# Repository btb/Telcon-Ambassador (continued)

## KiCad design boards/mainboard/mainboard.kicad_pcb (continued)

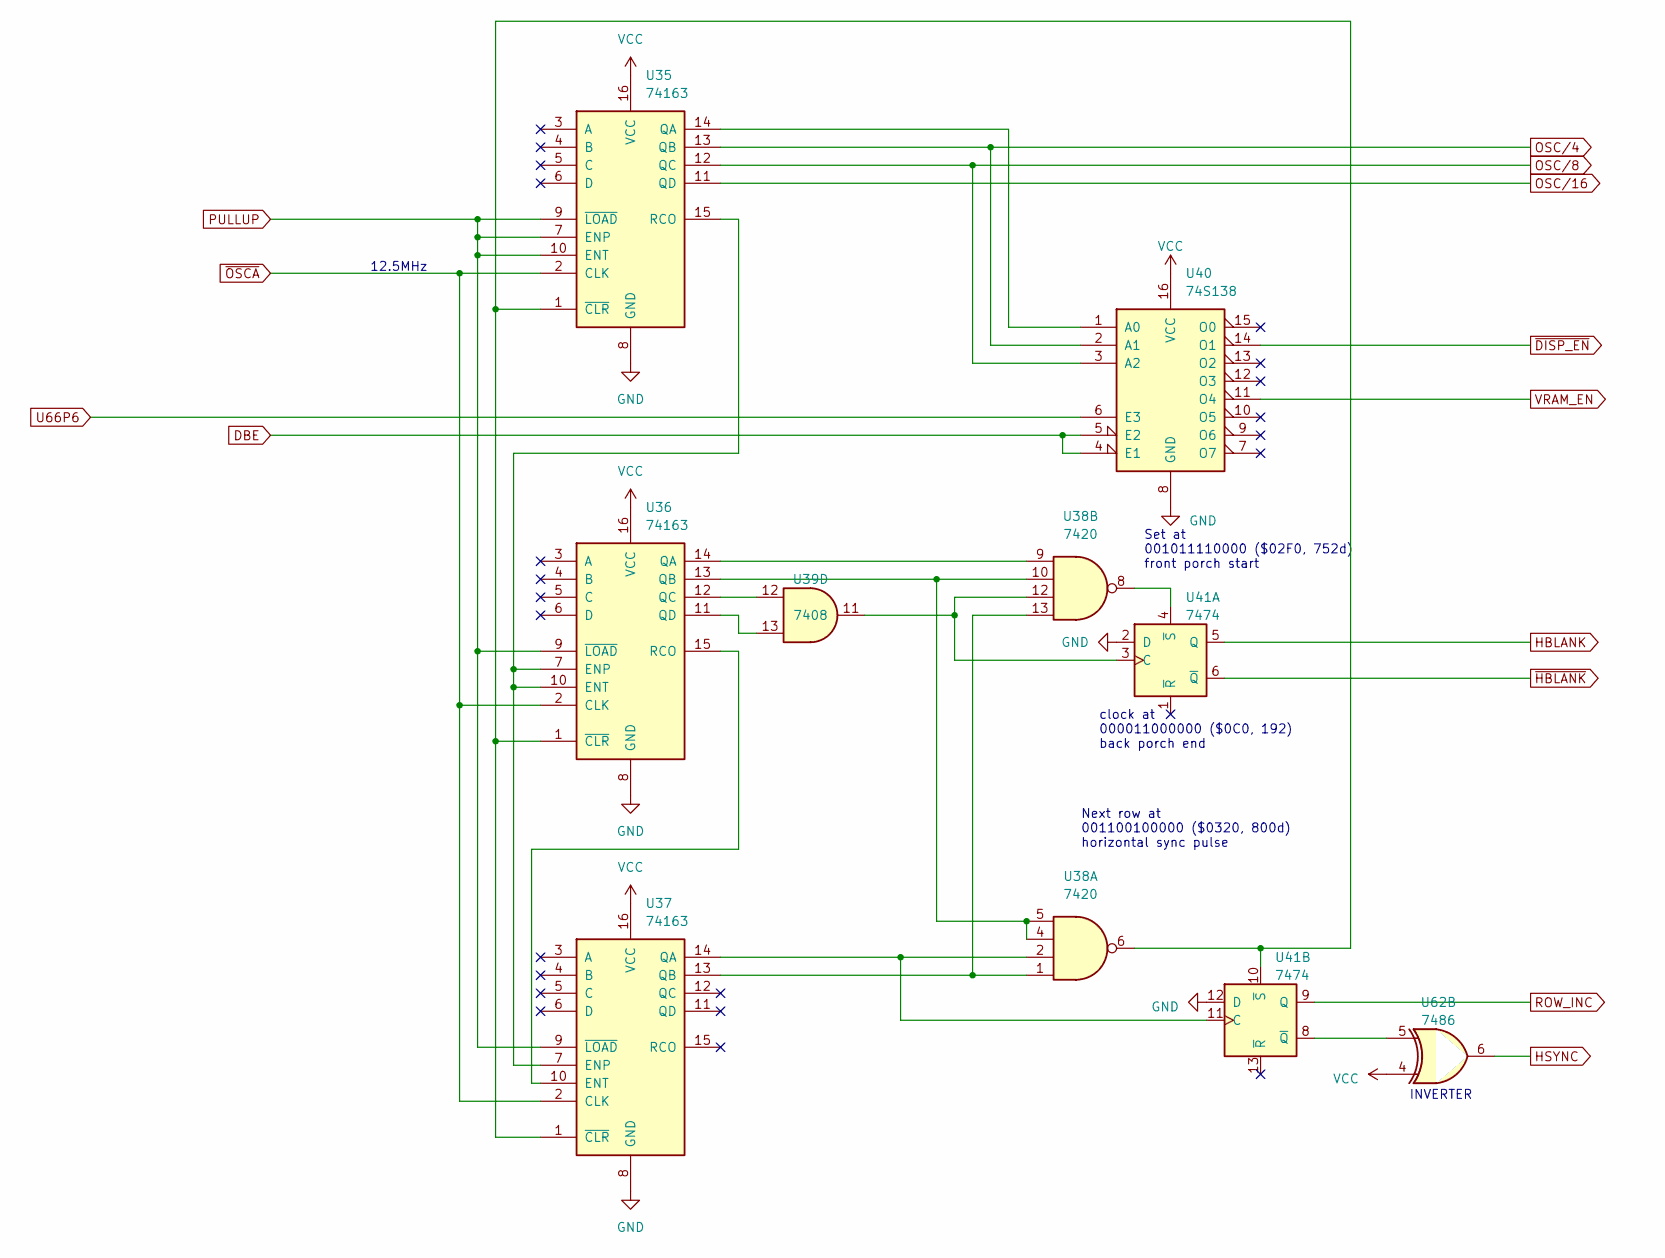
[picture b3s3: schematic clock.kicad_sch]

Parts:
U35, U36, U37: 74163; DIP-16_W7.62mm
U38: 7420; DIP-14_W7.62mm
U39: 7408; DIP-14_W7.62mm
U40: 74S138; DIP-16_W7.62mm
U41: 7474; DIP-14_W7.62mm
U62: 7486; DIP-14_W7.62mm

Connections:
DBE: U40.4 (E1), U40.5 (E2); also elsewhere on the board
GND: U35.8 (GND), U36.8 (GND), U37.8 (GND), U40.8 (GND), U41.2 (D), U41.12 (D); also elsewhere on the board
HBLANK: U41.5 (Q); also elsewhere on the board
HSYNC: U62.6; also elsewhere on the board
unnamed: U35.14 (QA), U40.1 (A0)
unnamed: U35.15 (RCO), U36.7 (ENP), U36.10 (ENT), U37.7 (ENP)
unnamed: U35.1 (~CLR), U36.1 (~CLR), U37.1 (~CLR), U38.6, U41.10 (~S)
unnamed: U36.14 (QA), U38.9
unnamed: U36.13 (QB), U38.4, U38.5, U38.10
unnamed: U36.12 (QC), U39.12
unnamed: U36.11 (QD), U39.13
unnamed: U36.15 (RCO), U37.10 (ENT)
unnamed: U37.14 (QA), U38.2, U41.11 (C)
unnamed: U37.13 (QB), U38.1, U38.13
unnamed: U38.12, U39.11, U41.3 (C)
unnamed: U38.8, U41.4 (~S)
unnamed: U41.8 (~Q), U62.5
OSC/4: U35.13 (QB), U40.2 (A1); also elsewhere on the board
OSC/8: U35.12 (QC), U40.3 (A2); also elsewhere on the board
OSC/16: U35.11 (QD); also elsewhere on the board
PULLUP: U35.7 (ENP), U35.9 (~LOAD), U35.10 (ENT), U36.9 (~LOAD), U37.9 (~LOAD); also elsewhere on the board
ROW_INC: U41.9 (Q); also elsewhere on the board
U66P6: U40.6 (E3); also elsewhere on the board
VCC: U35.16 (VCC), U36.16 (VCC), U37.16 (VCC), U40.16 (VCC), U62.4; also elsewhere on the board
VRAM_EN: U40.11 (O4); also elsewhere on the board
~DISP_EN: U40.14 (O1); also elsewhere on the board
~HBLANK: U41.6 (~Q); also elsewhere on the board
~OSCA: U35.2 (CLK), U36.2 (CLK), U37.2 (CLK); also elsewhere on the board

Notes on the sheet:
Next row at 001100100000 ($0320, 800d) horizontal sync pulse
INVERTER
12.5MHz
clock at 000011000000 ($0C0, 192) back porch end
Set at 001011110000 ($02F0, 752d) front porch start

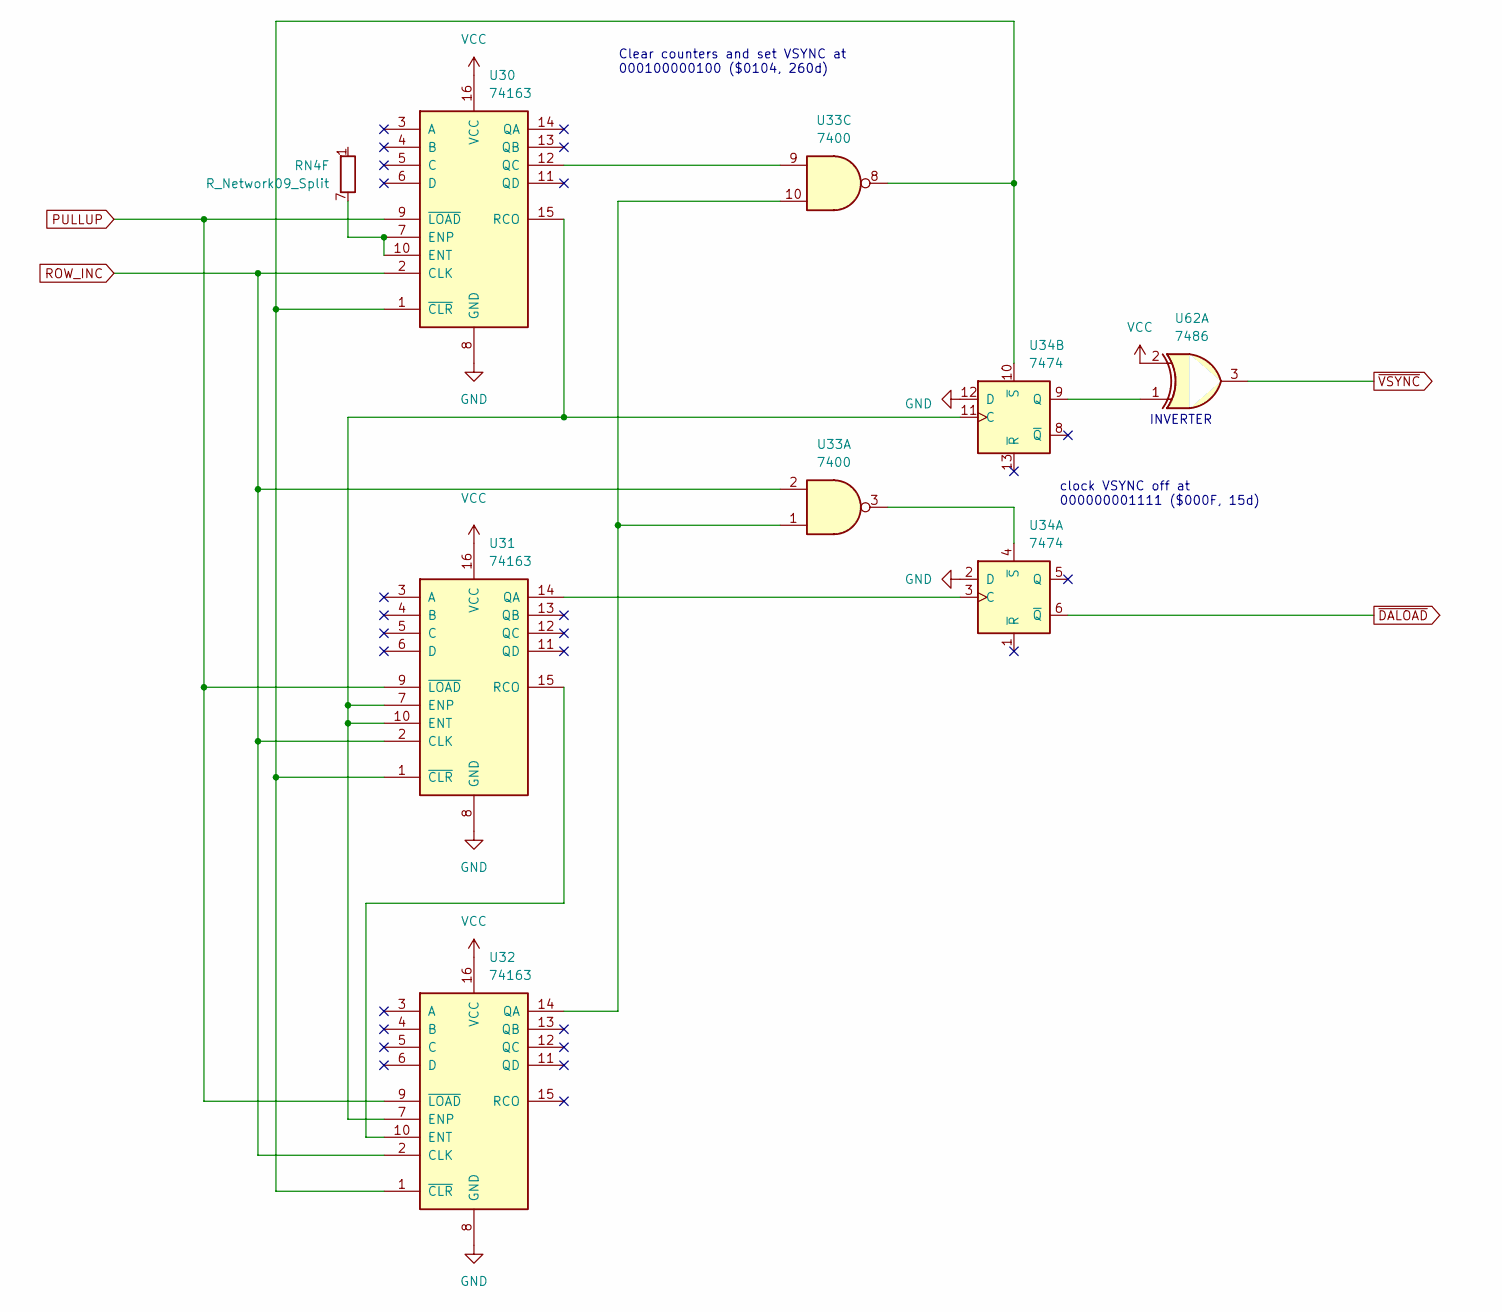
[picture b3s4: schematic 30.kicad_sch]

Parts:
RN4: R_Network09_Split; R_Array_SIP10
U30, U31, U32: 74163; DIP-16_W7.62mm
U33: 7400; DIP-14_W7.62mm
U34: 7474; DIP-14_W7.62mm
U62: 7486; DIP-14_W7.62mm

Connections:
GND: U30.8 (GND), U31.8 (GND), U32.8 (GND), U34.2 (D), U34.12 (D); also elsewhere on the board
unnamed: RN4.7 (R6.2), U30.7 (ENP), U30.10 (ENT)
unnamed: U30.12 (QC), U33.9
unnamed: U30.15 (RCO), U31.7 (ENP), U31.10 (ENT), U32.7 (ENP), U34.11 (C)
unnamed: U30.1 (~CLR), U31.1 (~CLR), U32.1 (~CLR), U33.8, U34.10 (~S)
unnamed: U31.14 (QA), U34.3 (C)
unnamed: U31.15 (RCO), U32.10 (ENT)
unnamed: U32.14 (QA), U33.1, U33.10
unnamed: U33.3, U34.4 (~S)
unnamed: U34.9 (Q), U62.1
PULLUP: U30.9 (~LOAD), U31.9 (~LOAD), U32.9 (~LOAD); also elsewhere on the board
ROW_INC: U30.2 (CLK), U31.2 (CLK), U32.2 (CLK), U33.2; also elsewhere on the board
VCC: U30.16 (VCC), U31.16 (VCC), U32.16 (VCC), U62.2; also elsewhere on the board
~DALOAD: U34.6 (~Q); also elsewhere on the board
~VSYNC: U62.3; also elsewhere on the board

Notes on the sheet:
INVERTER
Clear counters and set VSYNC at 000100000100 ($0104, 260d)
clock VSYNC off at 000000001111 ($000F, 15d)

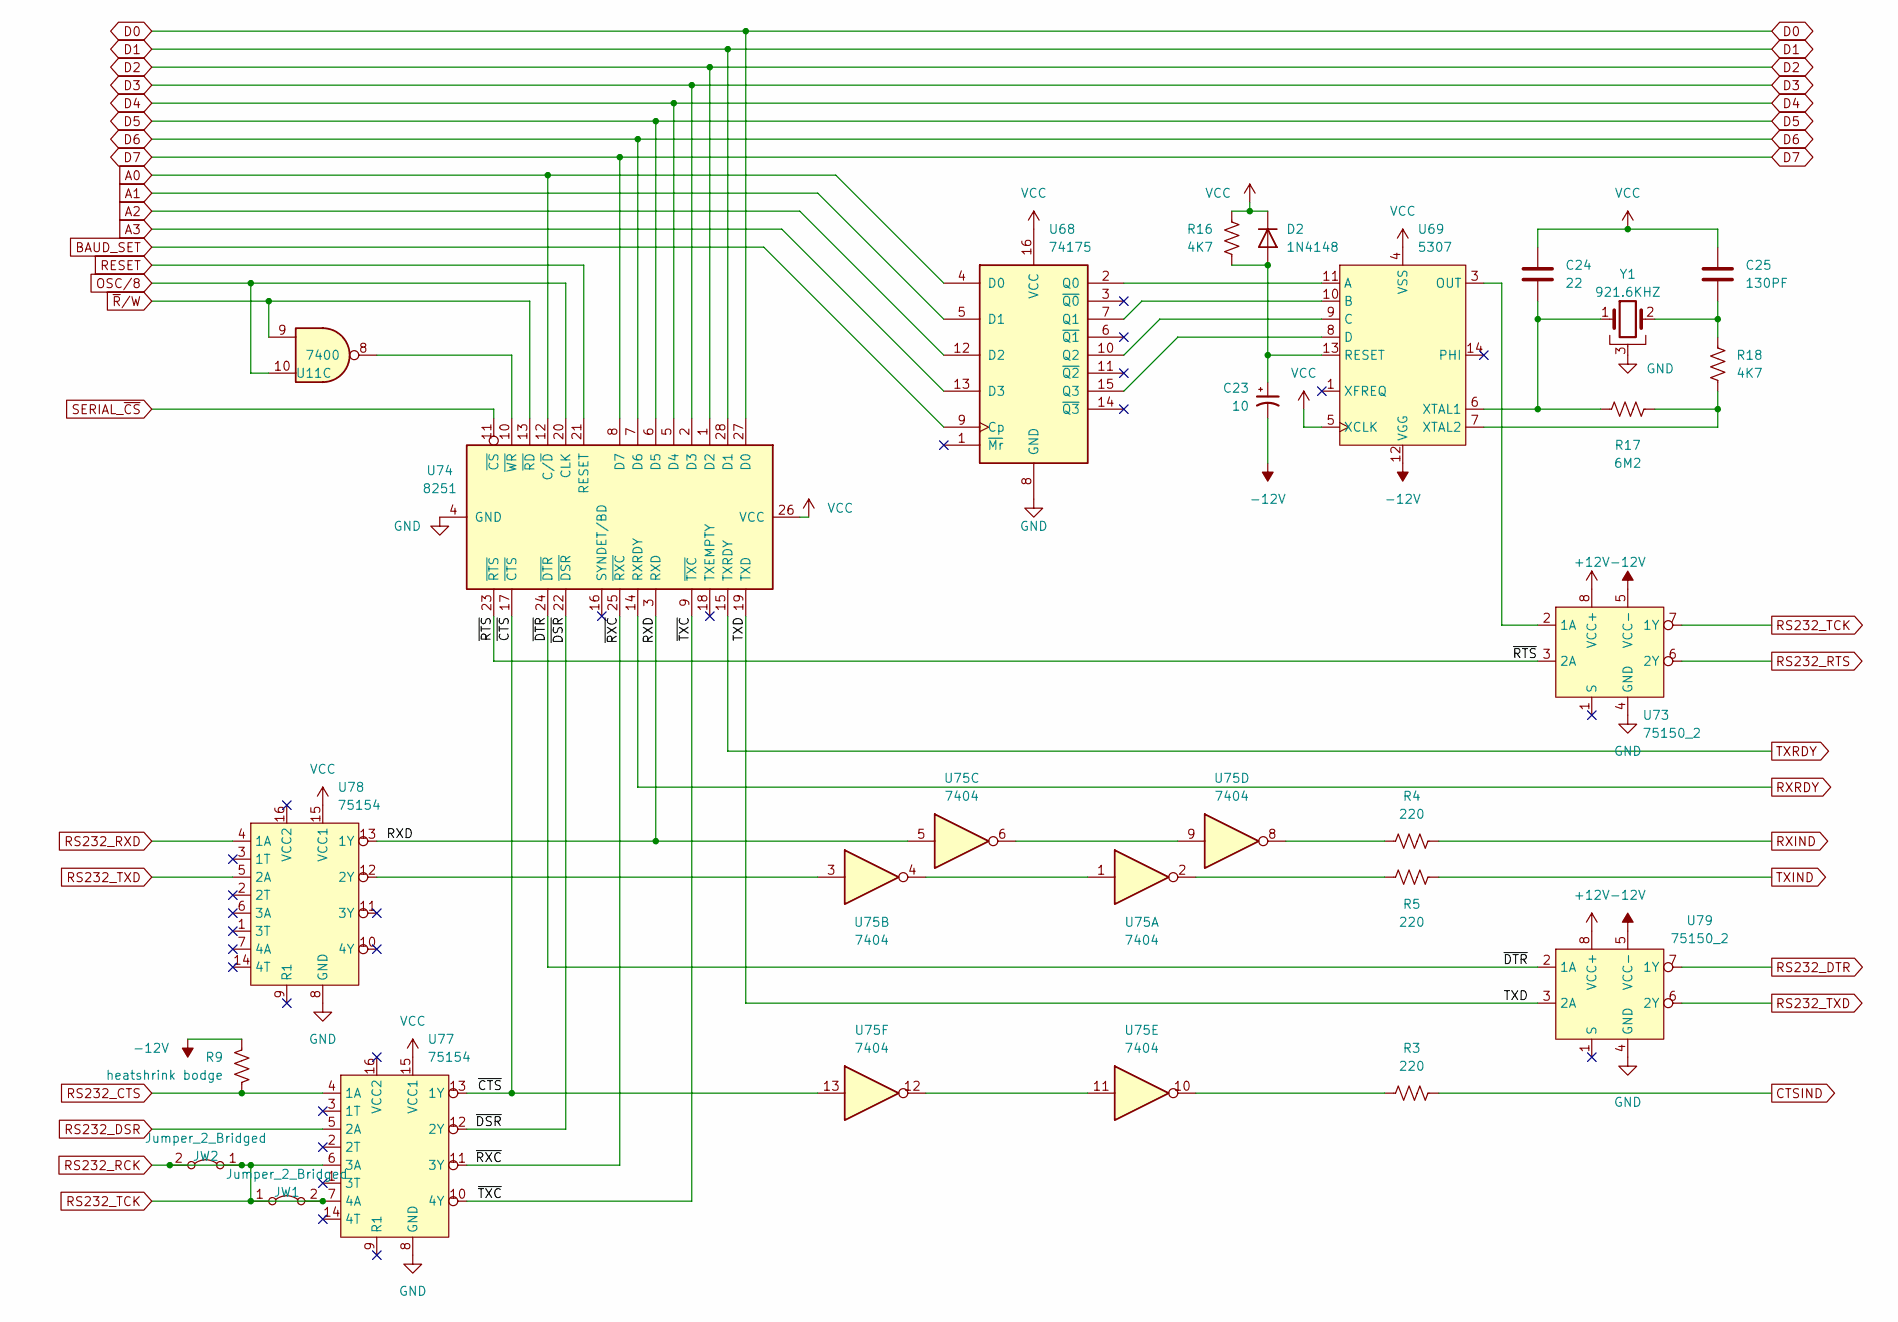
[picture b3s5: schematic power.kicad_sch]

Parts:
C23: 10; CP_Radial_Tantal_D4.5mm_P5.00mm
C24: 22; C_Disc_D11.0mm_W5.0mm_P7.50mm
C25: 130PF; C_Disc_D11.0mm_W5.0mm_P7.50mm
D2: 1N4148; D_DO-35_SOD27_P7.62mm_Horizontal
JW1: Jumper_2_Bridged; SolderWire-0.5sqmm_1x02_P10.16mm_D0.9mm_OD2.1mm
JW2: Jumper_2_Bridged; SolderWire-0.5sqmm_1x02_P12.7mm_D0.9mm_OD2.1mm
R3, R4, R5: 220; R_Axial_DIN0309_L9.0mm_D3.2mm_P12.70mm_Horizontal
R9: heatshrink bodge; R_Axial_DIN0309_L9.0mm_D3.2mm_P12.70mm_Horizontal
R16, R18: 4K7; R_Axial_DIN0309_L9.0mm_D3.2mm_P12.70mm_Horizontal
R17: 6M2; R_Axial_DIN0309_L9.0mm_D3.2mm_P12.70mm_Horizontal
U11: 7400; DIP-14_W7.62mm
U68: 74175; DIP-16_W7.62mm
U69: 5307; DIP-14_W7.62mm
U73, U79: 75150_2; DIP-8_W7.62mm
U74: 8251; DIP-28_W15.24mm
U75: 7404; DIP-14_W7.62mm
U77, U78: 75154; DIP-16_W7.62mm
Y1: 921.6KHZ; Crystal_HC33-U_Horizontal_1EP_style2

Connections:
+12V: U73.8 (VCC+), U79.8 (VCC+); also elsewhere on the board
-12V: C23.2, R9.2, U69.12 (VGG), U73.5 (VCC-), U79.5 (VCC-); also elsewhere on the board
/Serial/RXD: U74.3 (RXD), U75.5, U78.13 (1Y)
/Serial/TXD: U74.19 (TXD), U79.3 (2A)
/Serial/~CTS: U74.17 (~CTS), U75.13, U77.13 (1Y)
/Serial/~DSR: U74.22 (~DSR), U77.12 (2Y)
/Serial/~DTR: U74.24 (~DTR), U79.2 (1A)
/Serial/~RTS: U73.3 (2A), U74.23 (~RTS)
/Serial/~RXC: U74.25 (~RXC), U77.11 (3Y)
/Serial/~TXC: U74.9 (~TXC), U77.10 (4Y)
A0: U68.4 (D0), U74.12 (C/~D); also elsewhere on the board
A1: U68.5 (D1); also elsewhere on the board
A2: U68.12 (D2); also elsewhere on the board
A3: U68.13 (D3); also elsewhere on the board
BAUD_SET: U68.9 (Cp); also elsewhere on the board
CTSIND: R3.2; also elsewhere on the board
D0: U74.27 (D0); also elsewhere on the board
D1: U74.28 (D1); also elsewhere on the board
D2: U74.1 (D2); also elsewhere on the board
D3: U74.2 (D3); also elsewhere on the board
D4: U74.5 (D4); also elsewhere on the board
D5: U74.6 (D5); also elsewhere on the board
D6: U74.7 (D6); also elsewhere on the board
D7: U74.8 (D7); also elsewhere on the board
GND: U68.8 (GND), U73.4 (GND), U74.4 (GND), U77.8 (GND), U78.8 (GND), U79.4 (GND), Y1.3; also elsewhere on the board
unnamed: C25.1, R18.1, Y1.2
unnamed: C23.1, D2.2 (A), R16.1, U69.13 (RESET)
unnamed: R3.1, U75.10
unnamed: R4.1, U75.8
unnamed: R5.1, U75.2
unnamed: U68.2 (Q0), U69.11 (A)
unnamed: U68.7 (Q1), U69.10 (B)
unnamed: U68.10 (Q2), U69.9 (C)
unnamed: U68.15 (Q3), U69.8 (D)
unnamed: U69.3 (OUT), U73.2 (1A)
unnamed: C24.1, R17.1, U69.6 (XTAL1), Y1.1
unnamed: R17.2, R18.2, U69.7 (XTAL2)
unnamed: U11.8, U74.10 (~WR)
unnamed: U75.1, U75.4
unnamed: U75.6, U75.9
unnamed: U75.11, U75.12
unnamed: U75.3, U78.12 (2Y)
OSC/8: U11.10, U74.20 (CLK); also elsewhere on the board
RESET: U74.21 (RESET); also elsewhere on the board
RS232_CTS: R9.1, U77.4 (1A); also elsewhere on the board
RS232_DSR: U77.5 (2A); also elsewhere on the board
RS232_DTR: U79.7 (1Y); also elsewhere on the board
RS232_RCK: JW1.1 (A), JW1.2 (B), JW2.1 (A), JW2.2 (B), U73.7 (1Y), U77.6 (3A), U77.7 (4A); also elsewhere on the board
RS232_RTS: U73.6 (2Y); also elsewhere on the board
RS232_RXD: U78.4 (1A); also elsewhere on the board
RS232_TXD: U78.5 (2A), U79.6 (2Y); also elsewhere on the board
RXIND: R4.2; also elsewhere on the board
RXRDY: U74.14 (RXRDY); also elsewhere on the board
SERIAL_~CS: U74.11 (~CS); also elsewhere on the board
TXIND: R5.2; also elsewhere on the board
TXRDY: U74.15 (TXRDY); also elsewhere on the board
VCC: C24.2, C25.2, D2.1 (K), R16.2, U68.16 (VCC), U69.4 (VSS), U69.5 (XCLK), U74.26 (VCC), U77.15 (VCC1), U78.15 (VCC1); also elsewhere on the board
~R/W: U11.9, U74.13 (~RD); also elsewhere on the board

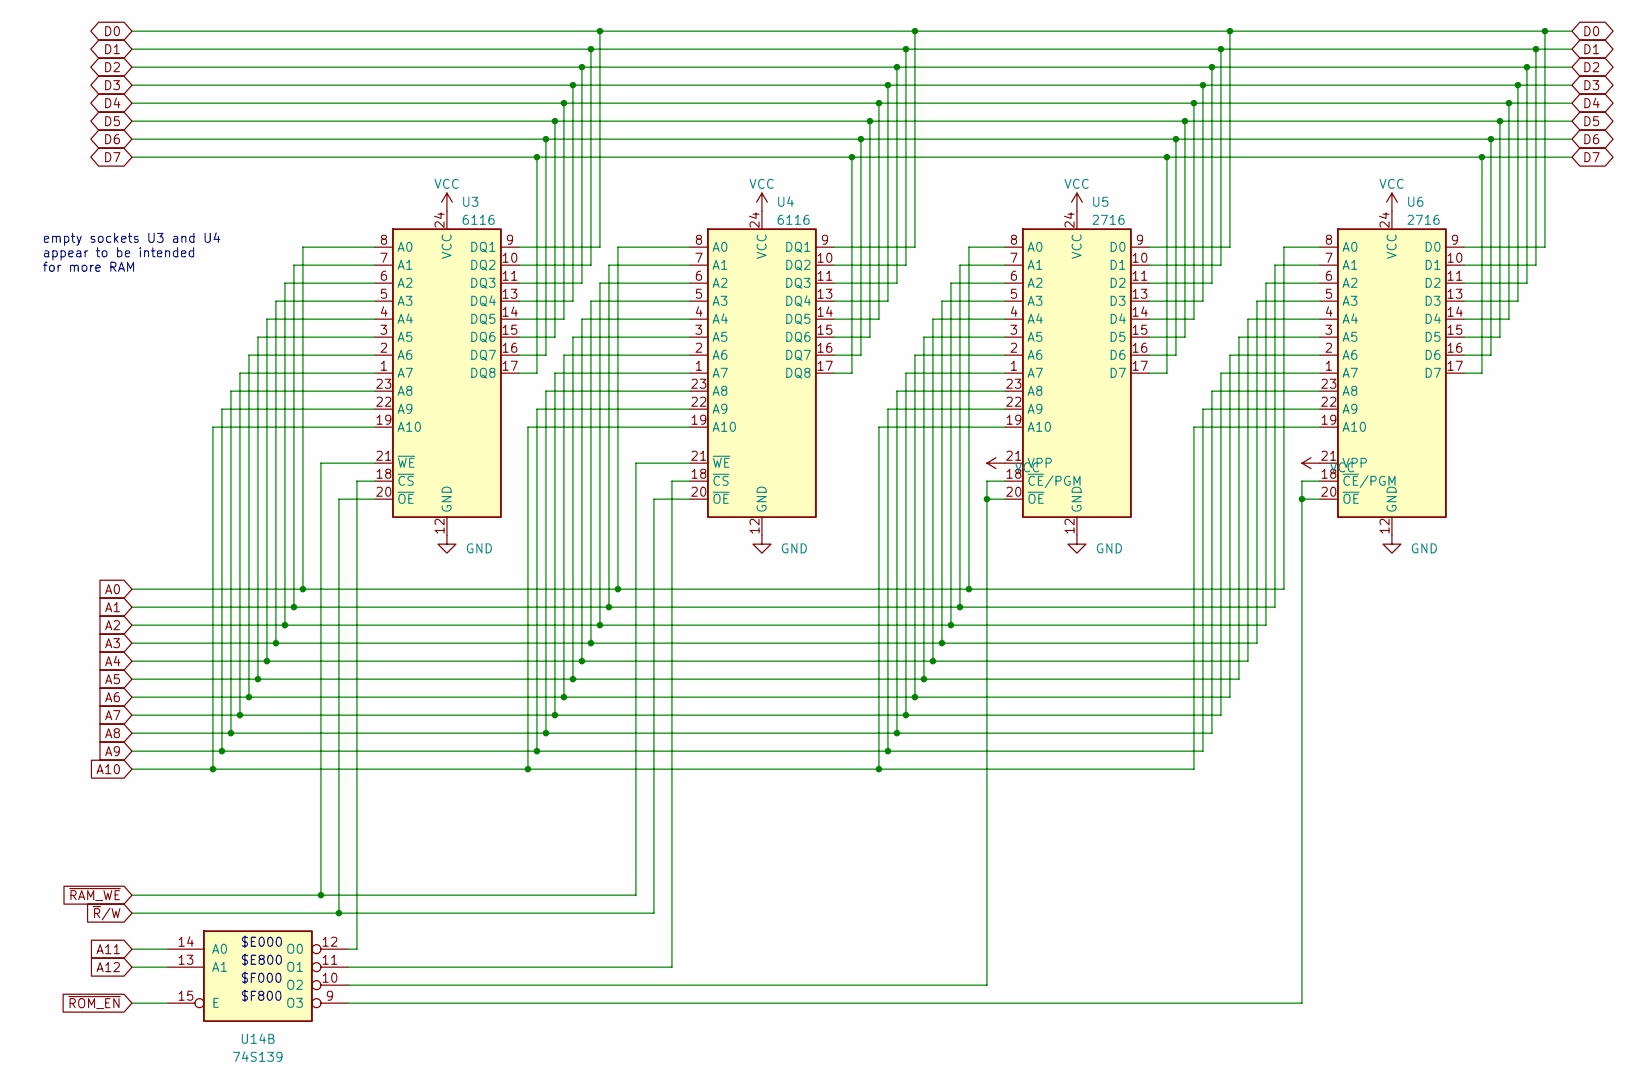
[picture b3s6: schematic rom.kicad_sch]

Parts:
U3, U4: 6116; DIP-24_W15.24mm
U5, U6: 2716; DIP-24_W15.24mm
U14: 74S139; DIP-16_W7.62mm

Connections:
A0: U3.8 (A0), U4.8 (A0), U5.8 (A0), U6.8 (A0); also elsewhere on the board
A1: U3.7 (A1), U4.7 (A1), U5.7 (A1), U6.7 (A1); also elsewhere on the board
A2: U3.6 (A2), U4.6 (A2), U5.6 (A2), U6.6 (A2); also elsewhere on the board
A3: U3.5 (A3), U4.5 (A3), U5.5 (A3), U6.5 (A3); also elsewhere on the board
A4: U3.4 (A4), U4.4 (A4), U5.4 (A4), U6.4 (A4); also elsewhere on the board
A5: U3.3 (A5), U4.3 (A5), U5.3 (A5), U6.3 (A5); also elsewhere on the board
A6: U3.2 (A6), U4.2 (A6), U5.2 (A6), U6.2 (A6); also elsewhere on the board
A7: U3.1 (A7), U4.1 (A7), U5.1 (A7), U6.1 (A7); also elsewhere on the board
A8: U3.23 (A8), U4.23 (A8), U5.23 (A8), U6.23 (A8); also elsewhere on the board
A9: U3.22 (A9), U4.22 (A9), U5.22 (A9), U6.22 (A9); also elsewhere on the board
A10: U3.19 (A10), U4.19 (A10), U5.19 (A10), U6.19 (A10); also elsewhere on the board
A11: U14.14 (A0); also elsewhere on the board
A12: U14.13 (A1); also elsewhere on the board
D0: U3.9 (DQ1), U4.9 (DQ1), U5.9 (D0), U6.9 (D0); also elsewhere on the board
D1: U3.10 (DQ2), U4.10 (DQ2), U5.10 (D1), U6.10 (D1); also elsewhere on the board
D2: U3.11 (DQ3), U4.11 (DQ3), U5.11 (D2), U6.11 (D2); also elsewhere on the board
D3: U3.13 (DQ4), U4.13 (DQ4), U5.13 (D3), U6.13 (D3); also elsewhere on the board
D4: U3.14 (DQ5), U4.14 (DQ5), U5.14 (D4), U6.14 (D4); also elsewhere on the board
D5: U3.15 (DQ6), U4.15 (DQ6), U5.15 (D5), U6.15 (D5); also elsewhere on the board
D6: U3.16 (DQ7), U4.16 (DQ7), U5.16 (D6), U6.16 (D6); also elsewhere on the board
D7: U3.17 (DQ8), U4.17 (DQ8), U5.17 (D7), U6.17 (D7); also elsewhere on the board
GND: U3.12 (GND), U4.12 (GND), U5.12 (GND), U6.12 (GND); also elsewhere on the board
unnamed: U3.18 (~CS), U14.12 (O0)
unnamed: U4.18 (~CS), U14.11 (O1)
unnamed: U5.18 (~CE/PGM), U5.20 (~OE), U14.10 (O2)
unnamed: U6.18 (~CE/PGM), U6.20 (~OE), U14.9 (O3)
VCC: U3.24 (VCC), U4.24 (VCC), U5.21 (VPP), U5.24 (VCC), U6.21 (VPP), U6.24 (VCC); also elsewhere on the board
~RAM_WE: U3.21 (~WE), U4.21 (~WE); also elsewhere on the board
~ROM_EN: U14.15 (E); also elsewhere on the board
~R/W: U3.20 (~OE), U4.20 (~OE); also elsewhere on the board

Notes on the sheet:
$F000
$F800
empty sockets U3 and U4 appear to be intended for more RAM
$E800
$E000

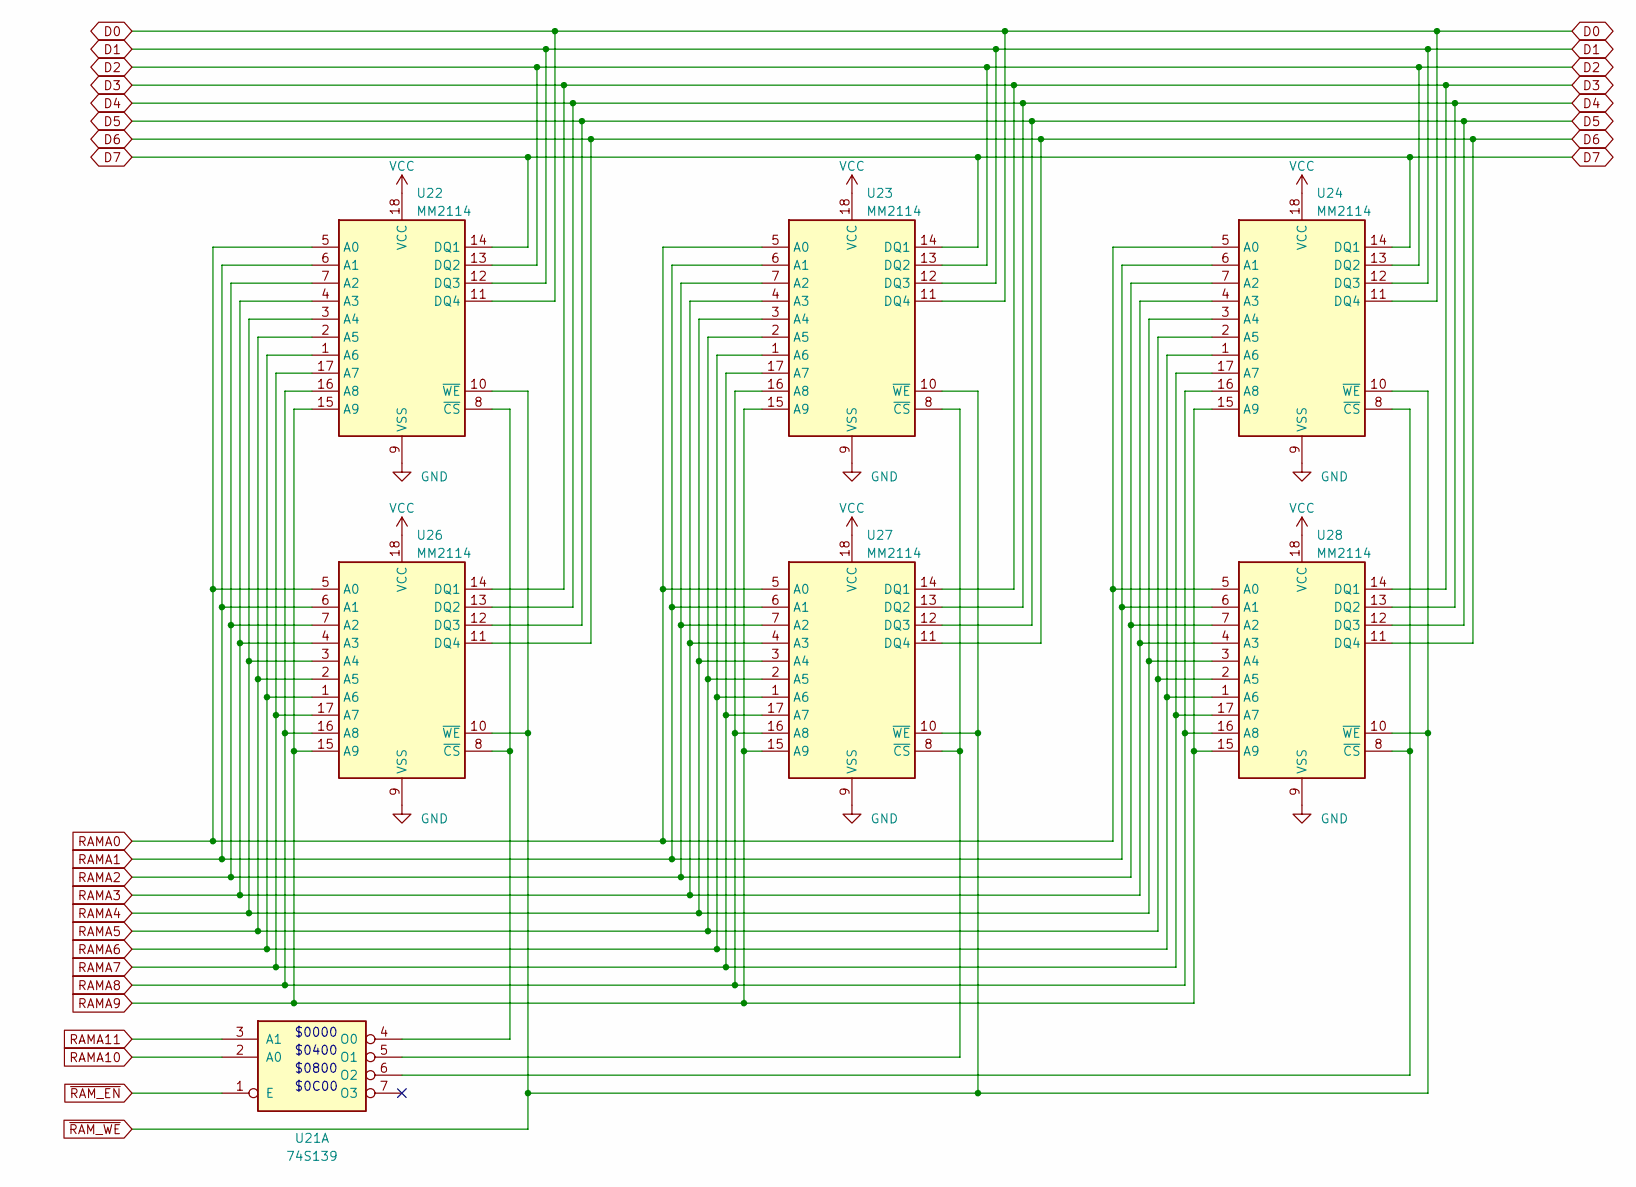
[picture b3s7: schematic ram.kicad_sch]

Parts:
U21: 74S139; DIP-16_W7.62mm
U22, U23, U24, U26, U27, U28: MM2114; DIP-18_W7.62mm

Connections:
D0: U22.11 (DQ4), U23.11 (DQ4), U24.11 (DQ4); also elsewhere on the board
D1: U22.12 (DQ3), U23.12 (DQ3), U24.12 (DQ3); also elsewhere on the board
D2: U22.13 (DQ2), U23.13 (DQ2), U24.13 (DQ2); also elsewhere on the board
D3: U26.14 (DQ1), U27.14 (DQ1), U28.14 (DQ1); also elsewhere on the board
D4: U26.13 (DQ2), U27.13 (DQ2), U28.13 (DQ2); also elsewhere on the board
D5: U26.12 (DQ3), U27.12 (DQ3), U28.12 (DQ3); also elsewhere on the board
D6: U26.11 (DQ4), U27.11 (DQ4), U28.11 (DQ4); also elsewhere on the board
D7: U22.14 (DQ1), U23.14 (DQ1), U24.14 (DQ1); also elsewhere on the board
GND: U22.9 (VSS), U23.9 (VSS), U24.9 (VSS), U26.9 (VSS), U27.9 (VSS), U28.9 (VSS); also elsewhere on the board
unnamed: U21.4 (O0), U22.8 (~CS), U26.8 (~CS)
unnamed: U21.5 (O1), U23.8 (~CS), U27.8 (~CS)
unnamed: U21.6 (O2), U24.8 (~CS), U28.8 (~CS)
RAMA0: U22.5 (A0), U23.5 (A0), U24.5 (A0), U26.5 (A0), U27.5 (A0), U28.5 (A0); also elsewhere on the board
RAMA1: U22.6 (A1), U23.6 (A1), U24.6 (A1), U26.6 (A1), U27.6 (A1), U28.6 (A1); also elsewhere on the board
RAMA2: U22.7 (A2), U23.7 (A2), U24.7 (A2), U26.7 (A2), U27.7 (A2), U28.7 (A2); also elsewhere on the board
RAMA3: U22.4 (A3), U23.4 (A3), U24.4 (A3), U26.4 (A3), U27.4 (A3), U28.4 (A3); also elsewhere on the board
RAMA4: U22.3 (A4), U23.3 (A4), U24.3 (A4), U26.3 (A4), U27.3 (A4), U28.3 (A4); also elsewhere on the board
RAMA5: U22.2 (A5), U23.2 (A5), U24.2 (A5), U26.2 (A5), U27.2 (A5), U28.2 (A5); also elsewhere on the board
RAMA6: U22.1 (A6), U23.1 (A6), U24.1 (A6), U26.1 (A6), U27.1 (A6), U28.1 (A6); also elsewhere on the board
RAMA7: U22.17 (A7), U23.17 (A7), U24.17 (A7), U26.17 (A7), U27.17 (A7), U28.17 (A7); also elsewhere on the board
RAMA8: U22.16 (A8), U23.16 (A8), U24.16 (A8), U26.16 (A8), U27.16 (A8), U28.16 (A8); also elsewhere on the board
RAMA9: U22.15 (A9), U23.15 (A9), U24.15 (A9), U26.15 (A9), U27.15 (A9), U28.15 (A9); also elsewhere on the board
RAMA10: U21.2 (A0); also elsewhere on the board
RAMA11: U21.3 (A1); also elsewhere on the board
VCC: U22.18 (VCC), U23.18 (VCC), U24.18 (VCC), U26.18 (VCC), U27.18 (VCC), U28.18 (VCC); also elsewhere on the board
~RAM_EN: U21.1 (E); also elsewhere on the board
~RAM_WE: U22.10 (~WE), U23.10 (~WE), U24.10 (~WE), U26.10 (~WE), U27.10 (~WE), U28.10 (~WE); also elsewhere on the board

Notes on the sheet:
$0000
$0400
$0800
$0C00

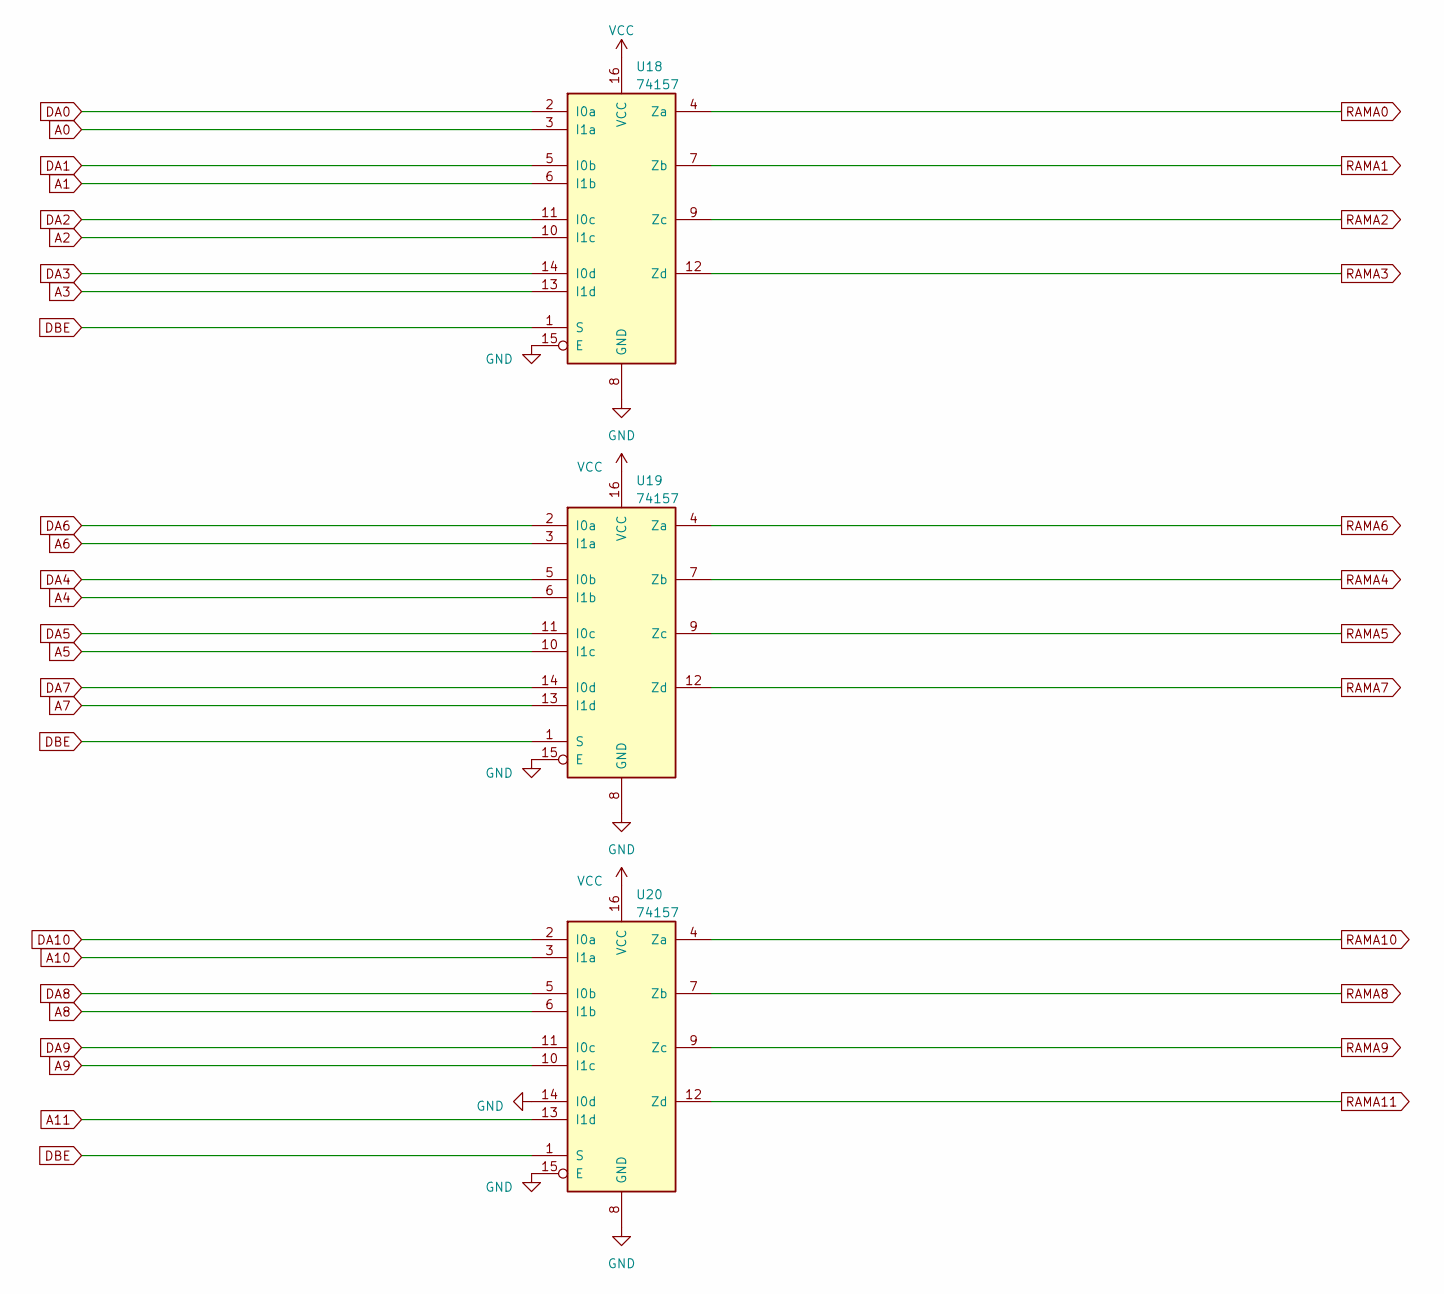
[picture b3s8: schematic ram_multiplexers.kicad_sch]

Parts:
U18, U19, U20: 74157; DIP-16_W7.62mm

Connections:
A0: U18.3 (I1a); also elsewhere on the board
A1: U18.6 (I1b); also elsewhere on the board
A2: U18.10 (I1c); also elsewhere on the board
A3: U18.13 (I1d); also elsewhere on the board
A4: U19.6 (I1b); also elsewhere on the board
A5: U19.10 (I1c); also elsewhere on the board
A6: U19.3 (I1a); also elsewhere on the board
A7: U19.13 (I1d); also elsewhere on the board
A8: U20.6 (I1b); also elsewhere on the board
A9: U20.10 (I1c); also elsewhere on the board
A10: U20.3 (I1a); also elsewhere on the board
A11: U20.13 (I1d); also elsewhere on the board
DA0: U18.2 (I0a); also elsewhere on the board
DA1: U18.5 (I0b); also elsewhere on the board
DA2: U18.11 (I0c); also elsewhere on the board
DA3: U18.14 (I0d); also elsewhere on the board
DA4: U19.5 (I0b); also elsewhere on the board
DA5: U19.11 (I0c); also elsewhere on the board
DA6: U19.2 (I0a); also elsewhere on the board
DA7: U19.14 (I0d); also elsewhere on the board
DA8: U20.5 (I0b); also elsewhere on the board
DA9: U20.11 (I0c); also elsewhere on the board
DA10: U20.2 (I0a); also elsewhere on the board
DBE: U18.1 (S), U19.1 (S), U20.1 (S); also elsewhere on the board
GND: U18.8 (GND), U18.15 (E), U19.8 (GND), U19.15 (E), U20.8 (GND), U20.14 (I0d), U20.15 (E); also elsewhere on the board
RAMA0: U18.4 (Za); also elsewhere on the board
RAMA1: U18.7 (Zb); also elsewhere on the board
RAMA2: U18.9 (Zc); also elsewhere on the board
RAMA3: U18.12 (Zd); also elsewhere on the board
RAMA4: U19.7 (Zb); also elsewhere on the board
RAMA5: U19.9 (Zc); also elsewhere on the board
RAMA6: U19.4 (Za); also elsewhere on the board
RAMA7: U19.12 (Zd); also elsewhere on the board
RAMA8: U20.7 (Zb); also elsewhere on the board
RAMA9: U20.9 (Zc); also elsewhere on the board
RAMA10: U20.4 (Za); also elsewhere on the board
RAMA11: U20.12 (Zd); also elsewhere on the board
VCC: U18.16 (VCC), U19.16 (VCC), U20.16 (VCC); also elsewhere on the board

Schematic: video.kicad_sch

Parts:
R1: 3.9K; R_Axial_DIN0309_L9.0mm_D3.2mm_P12.70mm_Horizontal
U60: 2758; DIP-24_W15.24mm
U61: 74166; DIP-16_W7.62mm
U62: 7486; DIP-14_W7.62mm
U63: 7474; DIP-14_W7.62mm

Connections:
CBUF1: U60.5 (A3); also elsewhere on the board
CBUF2: U60.4 (A4); also elsewhere on the board
CBUF3: U60.3 (A5); also elsewhere on the board
CBUF4: U60.2 (A6); also elsewhere on the board
CBUF5: U60.1 (A7); also elsewhere on the board
CBUF6: U60.23 (A8); also elsewhere on the board
CBUF7: U60.22 (A9); also elsewhere on the board
CBUF8: U63.12 (D); also elsewhere on the board
GND: R1.1, U60.12 (GND), U60.18 (~CE), U60.19 (AR), U60.20 (~OE), U61.1 (Ds), U61.2 (A), U61.6 (CE), U61.8 (GND); also elsewhere on the board
LC0: U60.8 (A0); also elsewhere on the board
LC1: U60.7 (A1); also elsewhere on the board
LC2: U60.6 (A2); also elsewhere on the board
unnamed: U60.9 (D0), U61.3 (B)
unnamed: U60.10 (D1), U61.4 (C)
unnamed: U60.11 (D2), U61.5 (D)
unnamed: U60.13 (D3), U61.10 (E)
unnamed: U60.14 (D4), U61.11 (F)
unnamed: U60.15 (D5), U61.12 (G)
unnamed: U60.16 (D6), U61.14 (H)
unnamed: U61.13 (Qh), U62.13
unnamed: U62.8, U63.11 (C)
unnamed: U62.12, U63.9 (Q)
OSCB: U61.7 (Clk); also elsewhere on the board
VCC: R1.2, U60.21 (VPP), U60.24 (VCC), U61.16 (VCC), U62.9; also elsewhere on the board
VIDEO: U62.11; also elsewhere on the board
~CCLK: U61.15 (PE), U62.10; also elsewhere on the board
~LC3: U61.9 (Clr); also elsewhere on the board
~LCCLK: U63.13 (~R); also elsewhere on the board

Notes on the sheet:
ascii code of character (0-127)
inverse video
character clock
pixels in row of character

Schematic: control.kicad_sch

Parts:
U10, U53: 7408; DIP-14_W7.62mm
U11, U67: 7400; DIP-14_W7.62mm
U13, U14: 74S139; DIP-16_W7.62mm
U43, U51: 7404; DIP-14_W7.62mm
U64, U65, U66: 7474; DIP-14_W7.62mm

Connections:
A2: U13.2 (A0); also elsewhere on the board
A3: U13.3 (A1); also elsewhere on the board
A11: U14.2 (A0); also elsewhere on the board
A12: U14.3 (A1); also elsewhere on the board
A13: U13.14 (A0); also elsewhere on the board
A14: U13.13 (A1); also elsewhere on the board
A15: U11.5, U51.5; also elsewhere on the board
BAUD_SET: U13.12 (O0); also elsewhere on the board
DBE: U10.2; also elsewhere on the board
GND: U66.2 (D); also elsewhere on the board
LC3: U53.5; also elsewhere on the board
unnamed: U10.3, U11.2, U11.4, U67.2
unnamed: U13.1 (E), U13.11 (O1)
unnamed: U11.6, U13.15 (E)
unnamed: U13.10 (O2), U14.1 (E)
unnamed: U43.1, U67.8
unnamed: U51.6, U67.1
unnamed: U64.3 (C), U64.9 (Q), U66.3 (C)
unnamed: U64.2 (D), U65.6 (~Q)
unnamed: U65.3 (C), U65.9 (Q)
unnamed: U65.5 (Q), U66.4 (~S), U67.13
unnamed: U53.6, U65.12 (D)
unnamed: U67.3, U67.9
OSC/8: U64.11 (C), U65.11 (C); also elsewhere on the board
SERIAL_~CS: U13.5 (O1); also elsewhere on the board
U64: U64.5 (Q); also elsewhere on the board
U66P6: U66.6 (~Q); also elsewhere on the board
U67P11: U67.10, U67.11
VCC: U64.13 (~R), U65.2 (D), U65.10 (~S); also elsewhere on the board
VMA: U10.1; also elsewhere on the board
~DALOAD: U53.4; also elsewhere on the board
~DBE: U64.12 (D); also elsewhere on the board
~DISP_EN: U64.4 (~S); also elsewhere on the board
~IO_C_SEL: U13.7 (O3); also elsewhere on the board
~IO_D_SEL: U13.6 (O2); also elsewhere on the board
~POS79: U65.1 (~R); also elsewhere on the board
~RAM_EN: U43.2; also elsewhere on the board
~RAM_WE: U11.3; also elsewhere on the board
~ROM_EN: U13.9 (O3); also elsewhere on the board
~R/W: U11.1; also elsewhere on the board
~U64: U64.6 (~Q), U67.12; also elsewhere on the board

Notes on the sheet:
$E-F000
$C800
$x000
$D800
$A-B000
$x00A
$C000
$x004
$x008
$D000
$8-9000
$C-D000
